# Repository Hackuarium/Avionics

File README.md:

# 9 outputs and 2 inputs

ACT4088 like in bioreactor:

Power supply

- LMR50410-Q1
- https://www.ti.com/lit/ds/symlink/lmr50410-q1.pdf?HQS=dis-mous-null-mousermode-dsf-pf-null-wwe&ts=1698122939216&ref_url=https%253A%252F%252Fwww.mouser.ch%252F

SO-8

- https://www.diodes.com/assets/Datasheets/AP64100Q.pdf - 10 external components
- https://www.diodes.com/assets/Datasheets/AP64202Q.pdf - 7 external components
- https://www.mouser.ch/datasheet/2/389/l6982-2303627.pdf - 7 external components

SOT-89

- https://www.mouser.ch/datasheet/2/294/NJW4132_E-1917720.pdf - NJW4132

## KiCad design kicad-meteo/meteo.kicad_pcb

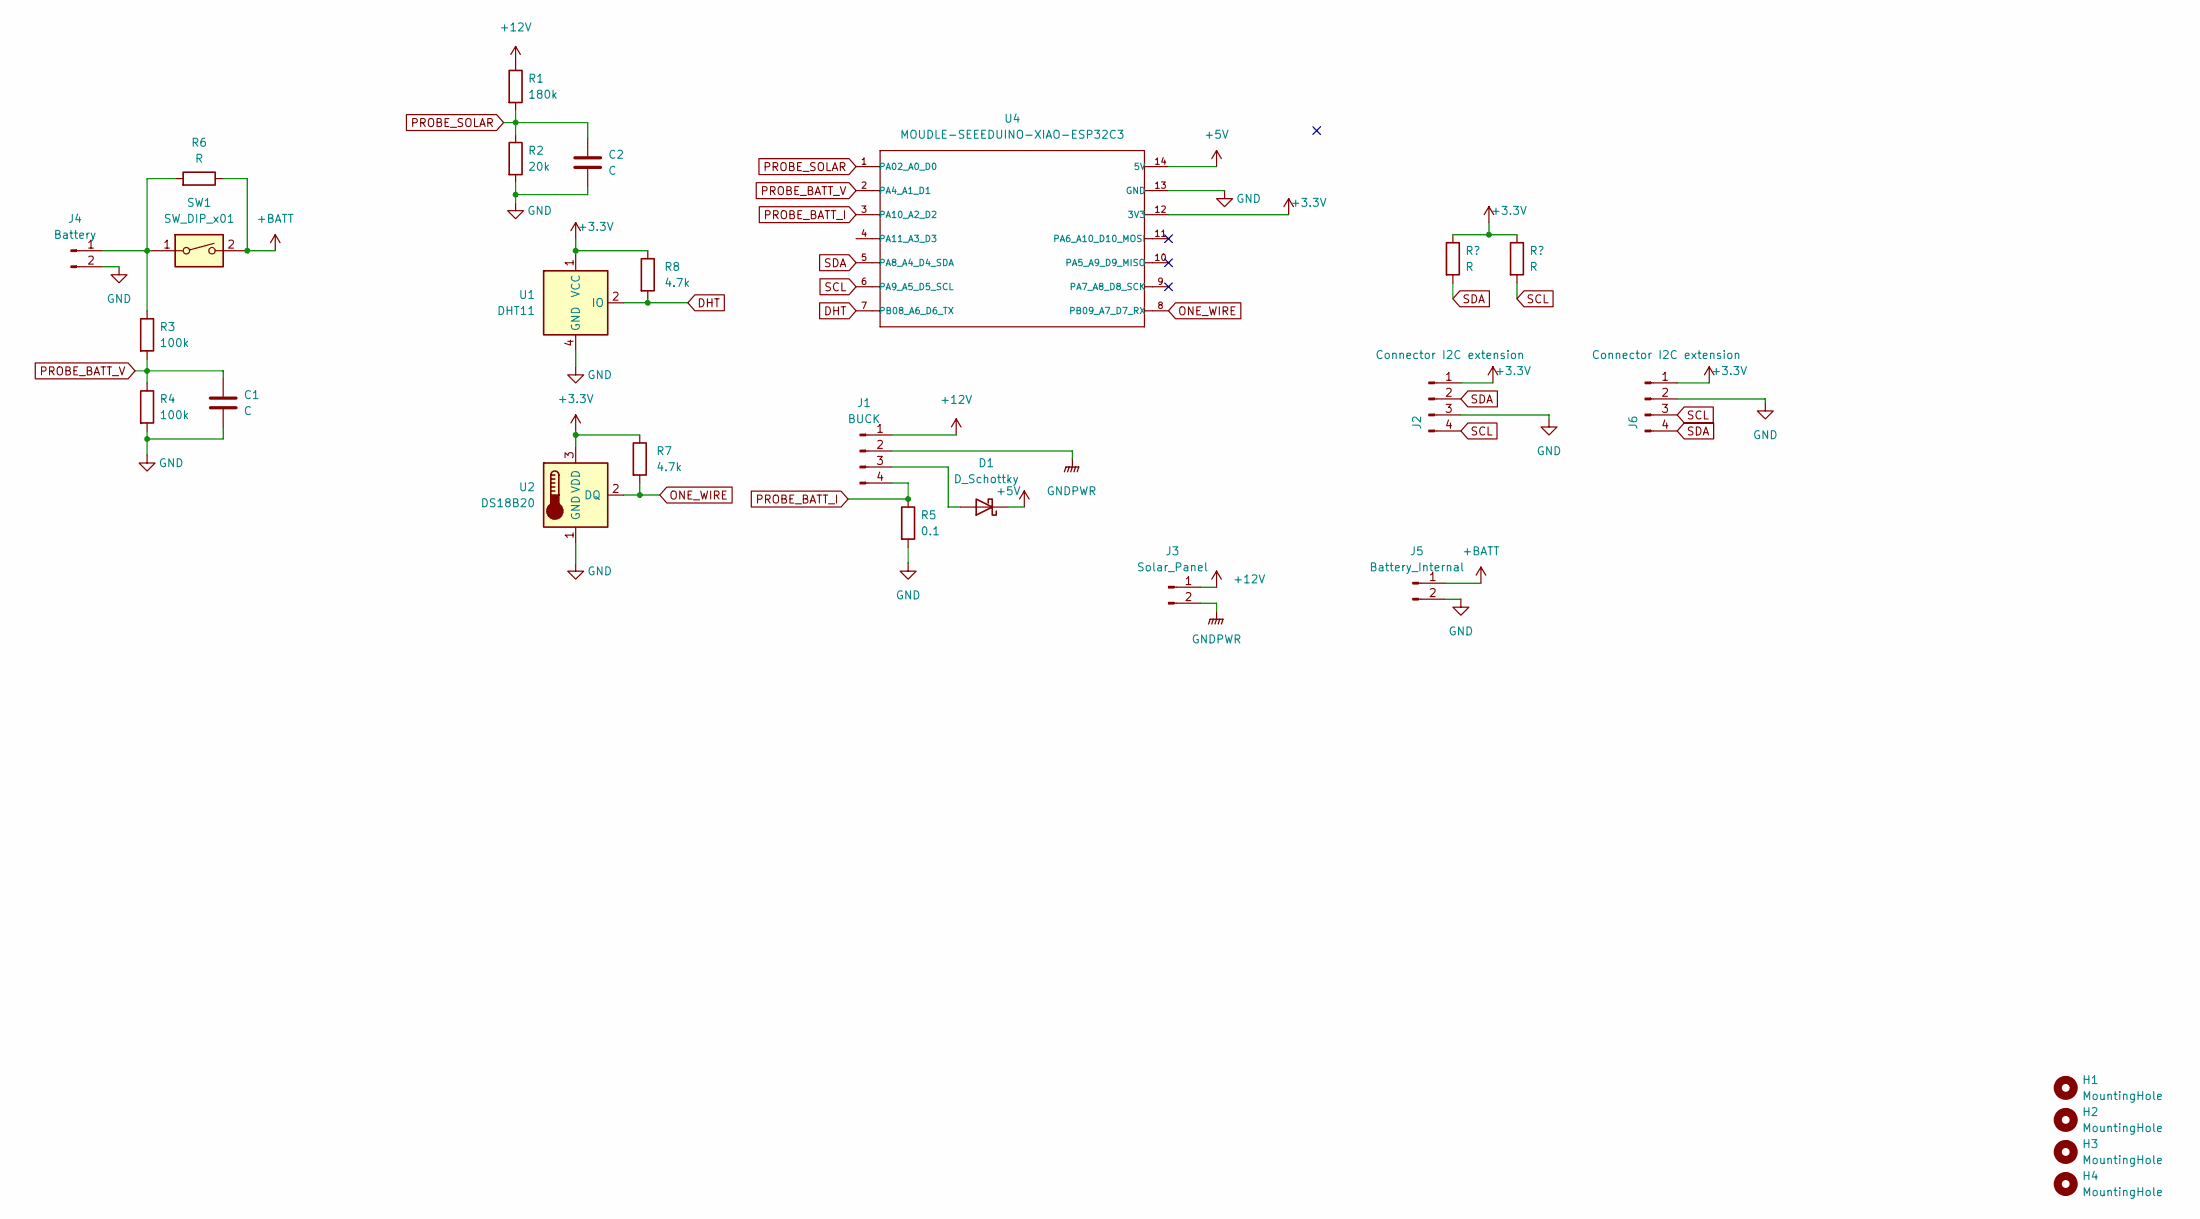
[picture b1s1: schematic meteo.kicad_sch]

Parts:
C1, C2: C; C_1206_3216Metric_Pad1.33x1.80mm_HandSolder
D1: D_Schottky; D_1206_3216Metric_Pad1.42x1.75mm_HandSolder
H1, H2, H3, H4: MountingHole; MountingHole_3.2mm_M3_ISO7380
J1: BUCK; BUCK 18x12mm
J2, J6: Connector I2C extension; PinHeader_1x04_P2.54mm_Vertical
J3: Solar_Panel; SolderWirePad_5.08x2
J4: Battery; SolderWirePad_5.08x2
J5: Battery_Internal; SolderWirePad_3x2
R1: 180k; R_1206_3216Metric_Pad1.30x1.75mm_HandSolder
R2: 20k; R_1206_3216Metric_Pad1.30x1.75mm_HandSolder
R3, R4: 100k; R_1206_3216Metric_Pad1.30x1.75mm_HandSolder
R5: 0.1; R_1206_3216Metric_Pad1.30x1.75mm_HandSolder
R6: R; R_1206_3216Metric_Pad1.30x1.75mm_HandSolder
R7, R8: 4.7k; R_1206_3216Metric_Pad1.30x1.75mm_HandSolder
SW1: SW_DIP_x01; SW_DIP_SPSTx01_Slide_9.78x4.72mm_W7.62mm_P2.54mm
U1: DHT11; Aosong_DHT11_5.5x12.0_P2.54mm
U2: DS18B20; PinHeader_1x03_P2.54mm_Vertical
U4: MOUDLE-SEEEDUINO-XIAO-ESP32C3; MOUDLE14P-SMD-2.54-21X17.8MM

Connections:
+3.3V: J2.1, J6.1, R7.1, R8.1, U1.1 (VCC), U2.3 (VDD), U4.12 (3V3)
+5V: D1.1 (K), U4.14 (5V)
+12V: J1.1, J3.1, R1.1
+BATT: J5.1, R6.1, SW1.2
DHT: R8.2, U1.2 (IO), U4.7 (PB08_A6_D6_TX)
GND: C1.2, C2.2, J2.3, J4.2, J5.2, J6.2, R2.2, R4.2, R5.2, U1.4 (GND), U2.1 (GND), U4.13 (GND)
GNDPWR: J1.2, J3.2
unnamed: D1.2 (A), J1.3
unnamed: J4.1, R3.1, R6.2, SW1.1
ONE_WIRE: R7.2, U2.2 (DQ), U4.8 (PB09_A7_D7_RX)
PROBE_BATT_I: J1.4, R5.1, U4.3 (PA10_A2_D2)
PROBE_BATT_V: C1.1, R3.2, R4.1, U4.2 (PA4_A1_D1)
PROBE_SOLAR: C2.1, R1.2, R2.1, U4.1 (PA02_A0_D0)
SCL: J2.4, J6.3, U4.6 (PA9_A5_D5_SCL)
SDA: J2.2, J6.4, U4.5 (PA8_A4_D4_SDA)

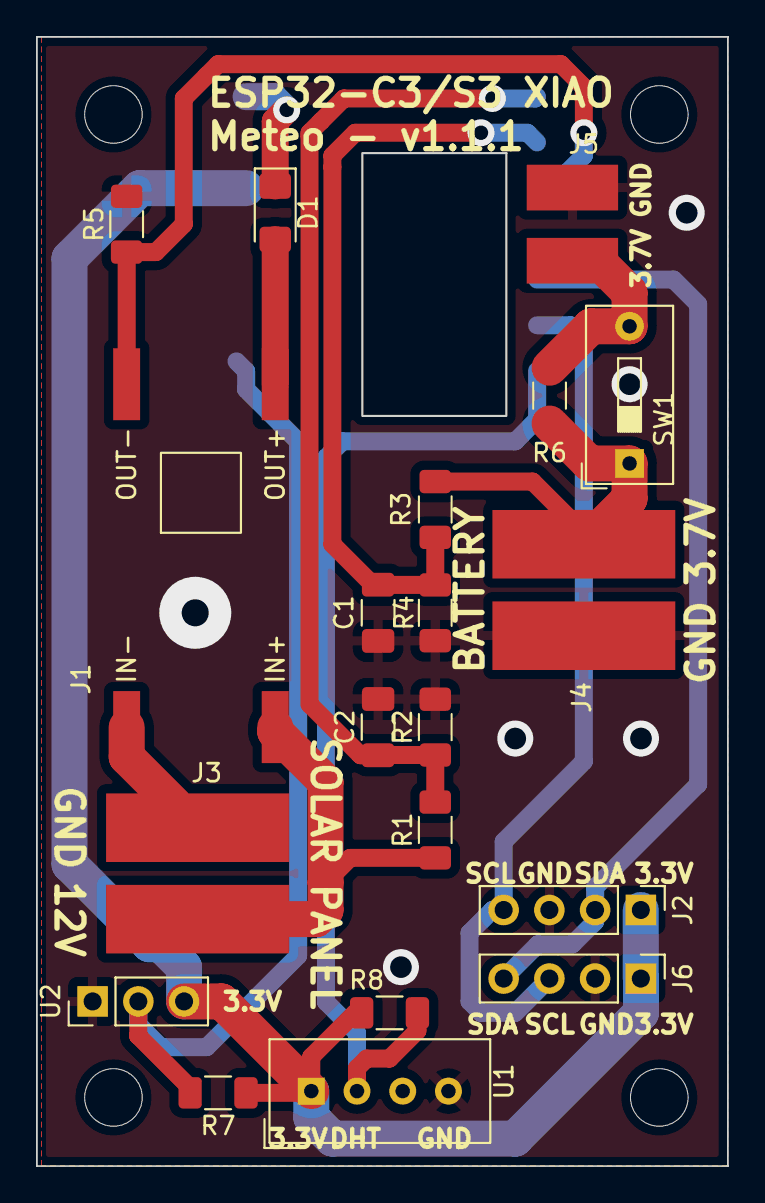
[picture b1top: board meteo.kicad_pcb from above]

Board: 2 copper layers, 38.4 x 62.7 mm, 25 parts (1 on the bottom side), 15 nets.

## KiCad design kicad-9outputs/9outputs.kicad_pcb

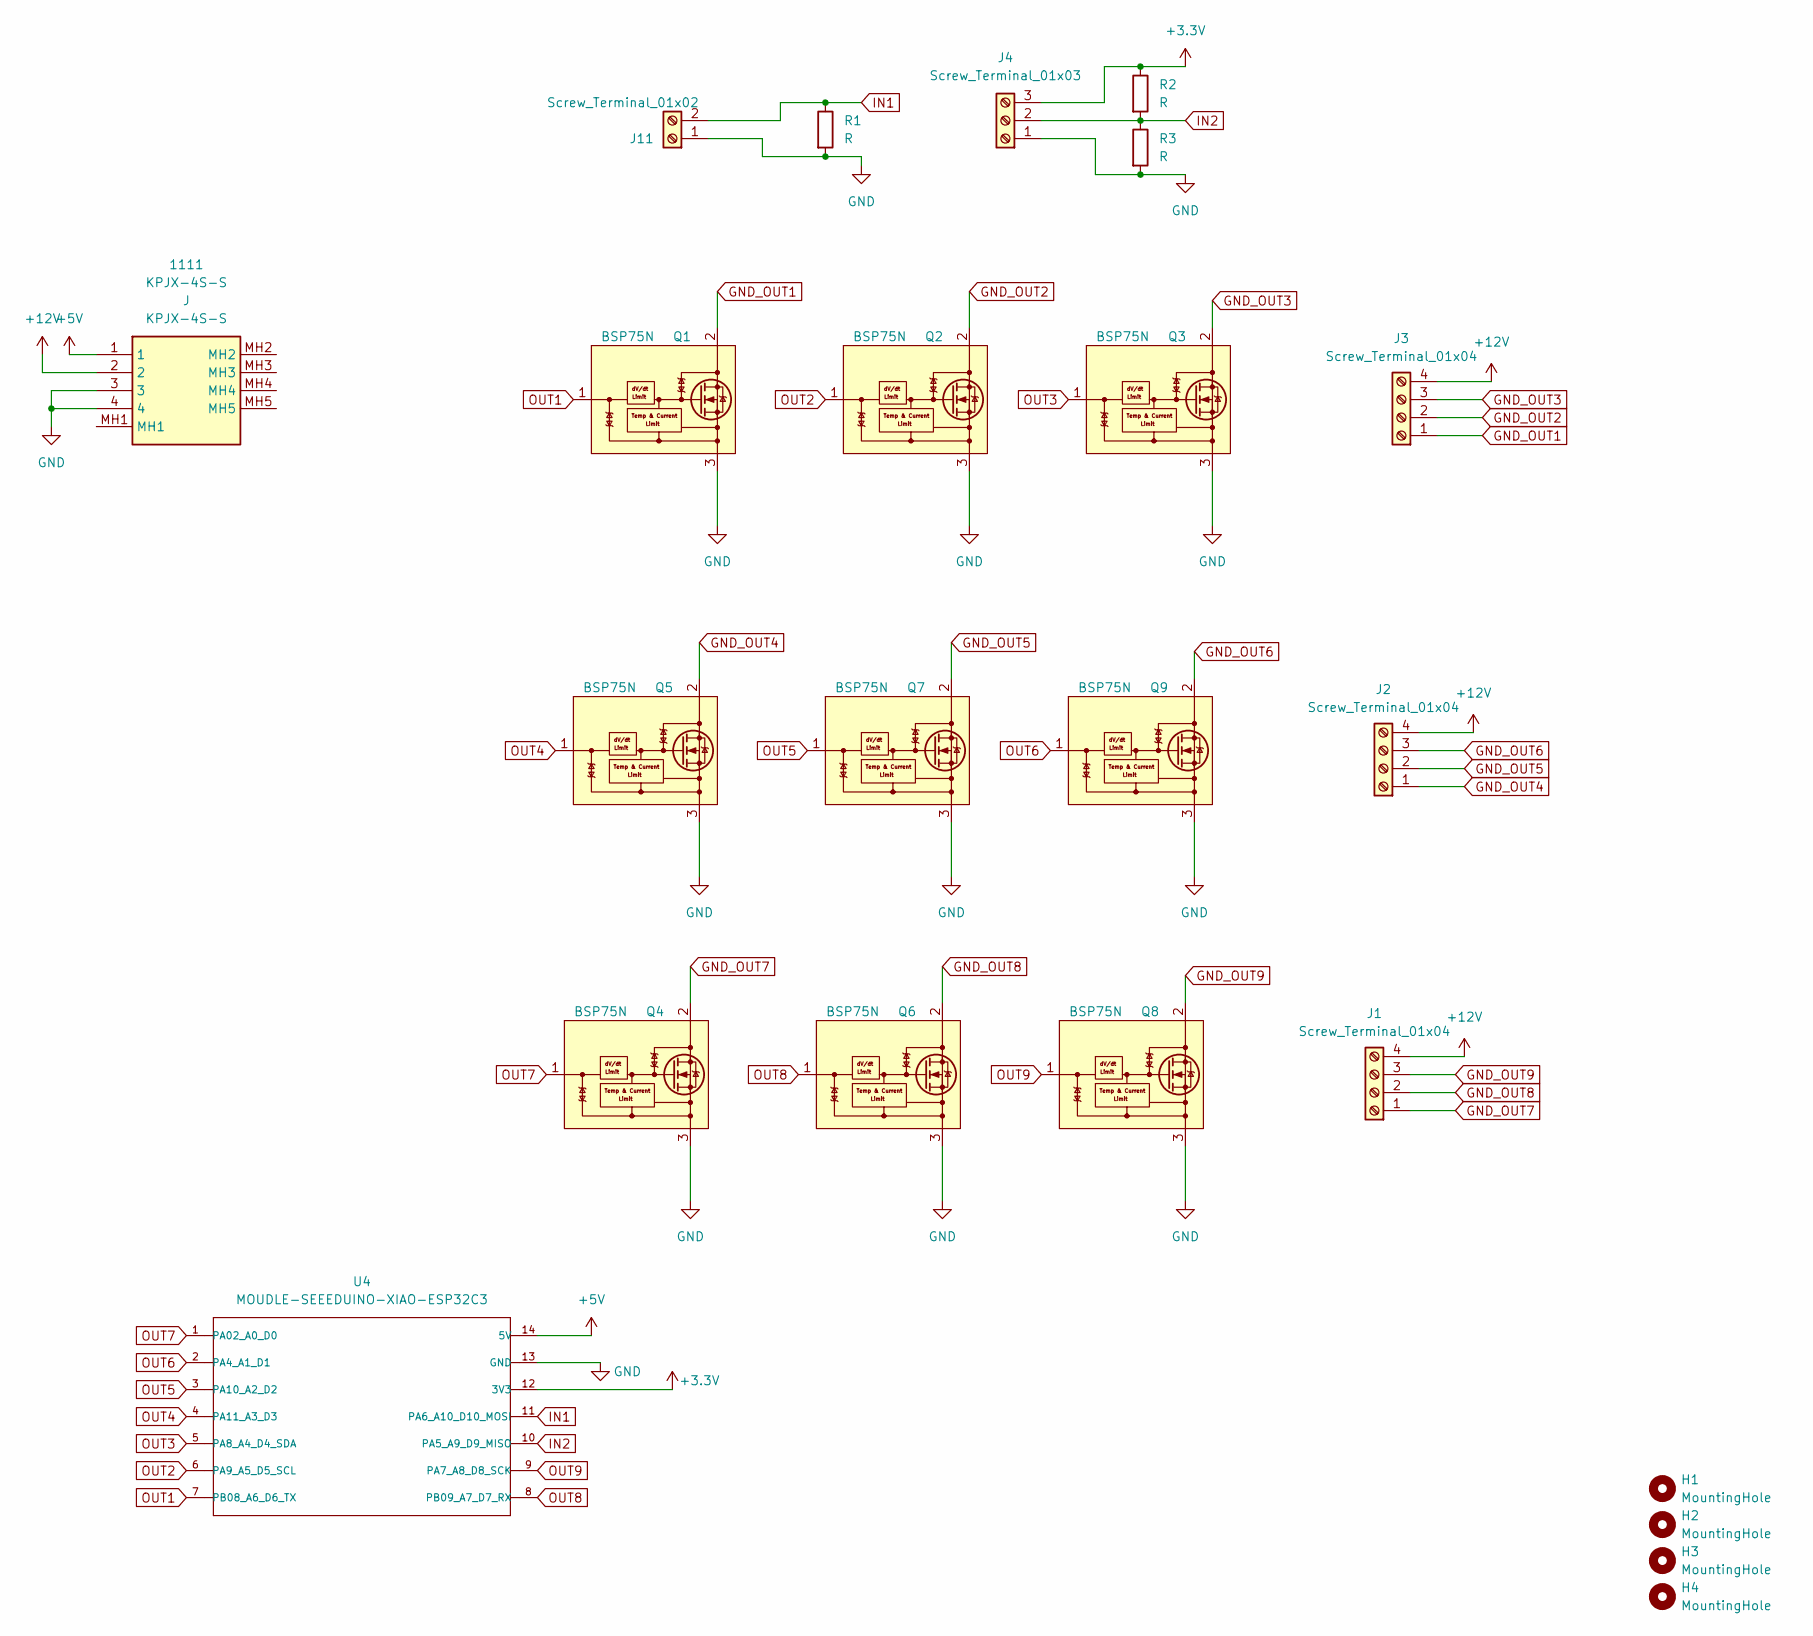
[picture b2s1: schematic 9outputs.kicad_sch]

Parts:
1111: KPJX-4S-S; KPJX4SS; Mouser Part Number 806-KPJX-4S-S
H1, H2, H3, H4: MountingHole; MountingHole_3.2mm_M3_ISO7380
J1, J2, J3: Screw_Terminal_01x04; TerminalBlock_MetzConnect_Type094_RT03504HBLU_1x04_P5.00mm_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
J4: Screw_Terminal_01x03; TerminalBlock_MetzConnect_Type094_RT03503HBLU_1x03_P5.00mm_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
J11: Screw_Terminal_01x02; TerminalBlock_MetzConnect_Type094_RT03502HBLU_1x02_P5.00mm_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
Q1, Q2, Q3, Q4, Q5, Q6, Q7, Q8, Q9: BSP75N; SOT-223
R1, R2, R3: R; R_1206_3216Metric_Pad1.30x1.75mm_HandSolder
U4: MOUDLE-SEEEDUINO-XIAO-ESP32C3; MOUDLE14P-SMD-2.54-21X17.8MM

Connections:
+3.3V: J4.3, R2.1, U4.12 (3V3)
+5V: 1111.1, U4.14 (5V)
+12V: 1111.2, J1.4, J2.4, J3.4
GND: 1111.3, 1111.4, J4.1, J11.1, Q1.3 (S), Q1.4 (S), Q2.3 (S), Q2.4 (S), Q3.3 (S), Q3.4 (S), Q4.3 (S), Q4.4 (S), Q5.3 (S), Q5.4 (S), Q6.3 (S), Q6.4 (S), Q7.3 (S), Q7.4 (S), Q8.3 (S), Q8.4 (S), Q9.3 (S), Q9.4 (S), R1.2, R3.2, U4.13 (GND)
GND_OUT1: J3.1, Q1.2 (D)
GND_OUT2: J3.2, Q2.2 (D)
GND_OUT3: J3.3, Q3.2 (D)
GND_OUT4: J2.1, Q5.2 (D)
GND_OUT5: J2.2, Q7.2 (D)
GND_OUT6: J2.3, Q9.2 (D)
GND_OUT7: J1.1, Q4.2 (D)
GND_OUT8: J1.2, Q6.2 (D)
GND_OUT9: J1.3, Q8.2 (D)
IN1: J11.2, R1.1, U4.11 (PA6_A10_D10_MOSI)
IN2: J4.2, R2.2, R3.1, U4.10 (PA5_A9_D9_MISO)
OUT1: Q1.1 (G), U4.7 (PB08_A6_D6_TX)
OUT2: Q2.1 (G), U4.6 (PA9_A5_D5_SCL)
OUT3: Q3.1 (G), U4.5 (PA8_A4_D4_SDA)
OUT4: Q5.1 (G), U4.4 (PA11_A3_D3)
OUT5: Q7.1 (G), U4.3 (PA10_A2_D2)
OUT6: Q9.1 (G), U4.2 (PA4_A1_D1)
OUT7: Q4.1 (G), U4.1 (PA02_A0_D0)
OUT8: Q6.1 (G), U4.8 (PB09_A7_D7_RX)
OUT9: Q8.1 (G), U4.9 (PA7_A8_D8_SCK)

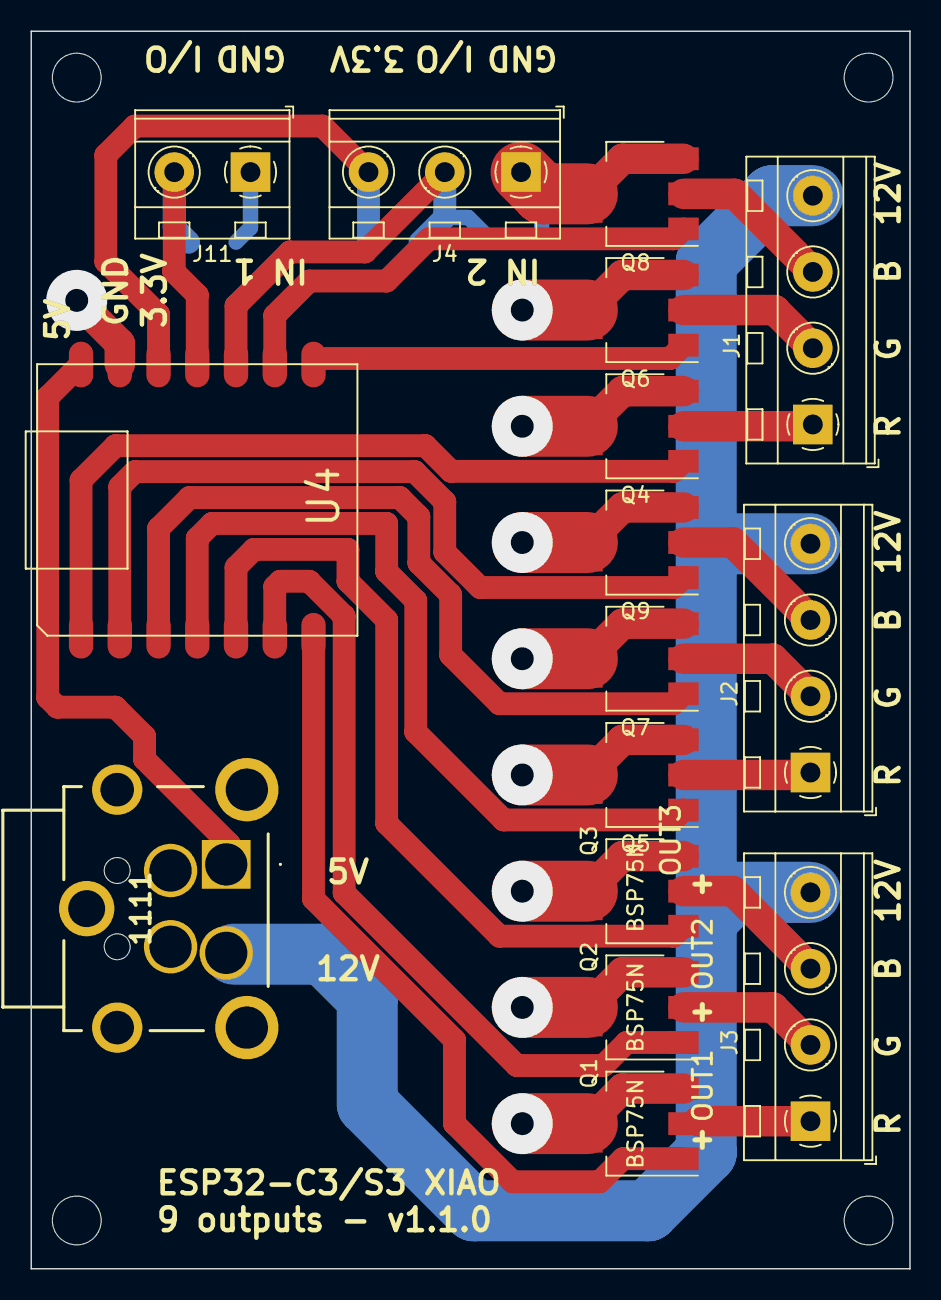
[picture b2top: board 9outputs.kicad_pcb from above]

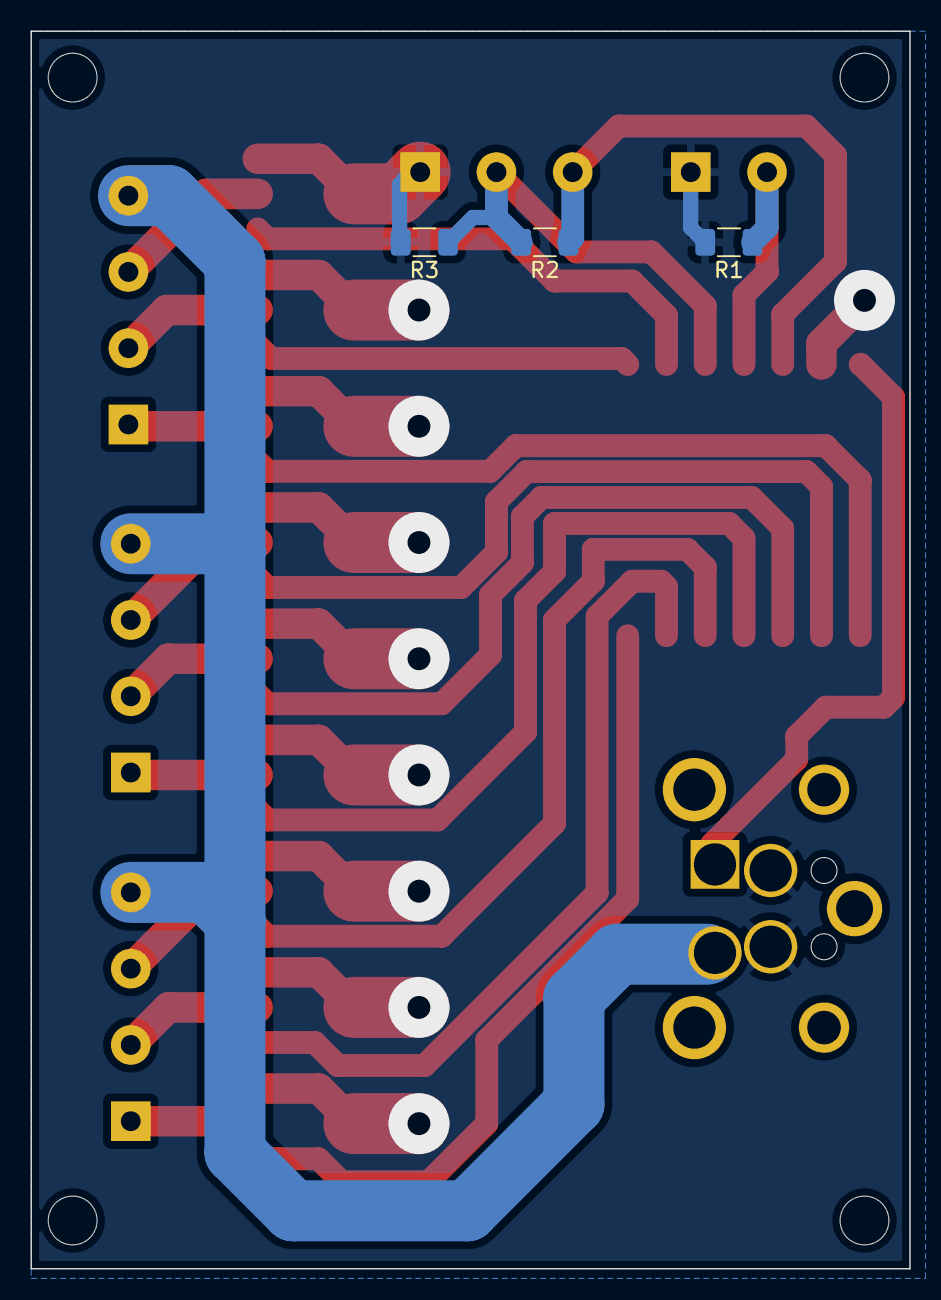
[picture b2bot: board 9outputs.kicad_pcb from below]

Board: 2 copper layers, 57.6 x 81.1 mm, 23 parts (3 on the bottom side), 24 nets.

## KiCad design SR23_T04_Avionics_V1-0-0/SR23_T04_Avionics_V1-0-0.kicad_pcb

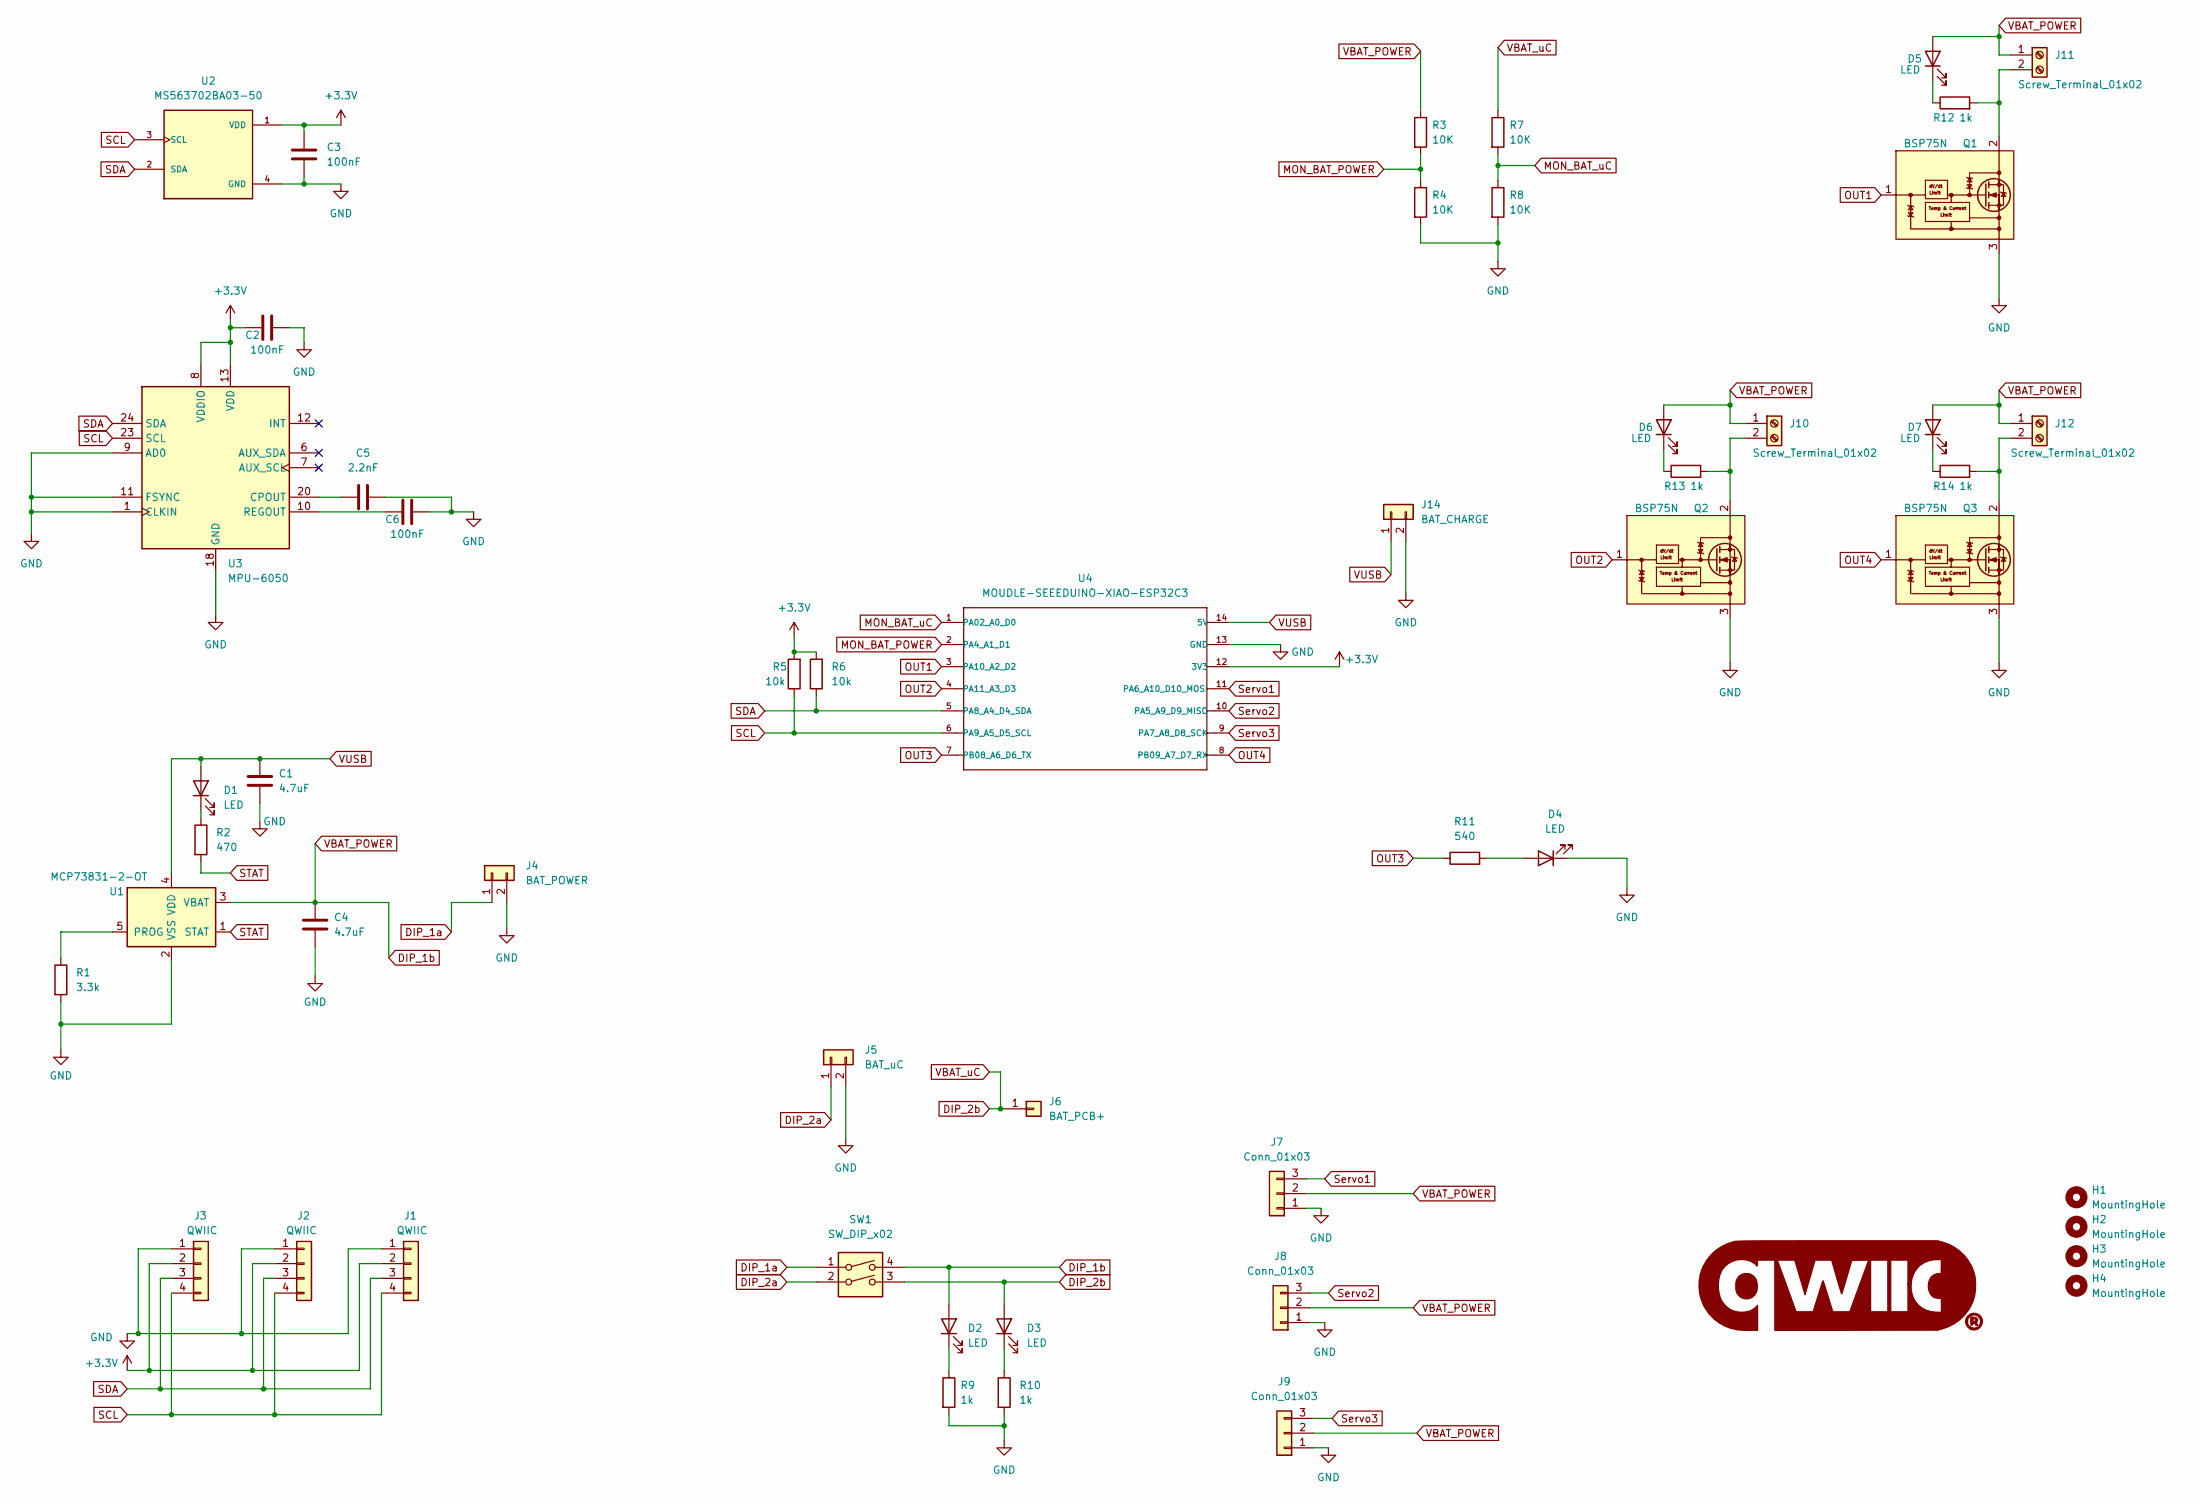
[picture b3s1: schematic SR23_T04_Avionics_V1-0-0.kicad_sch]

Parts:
C1, C4: 4.7uF; C_0805_2012Metric_Pad1.18x1.45mm_HandSolder
C2, C3, C6: 100nF; C_0805_2012Metric_Pad1.18x1.45mm_HandSolder
C5: 2.2nF; C_0805_2012Metric_Pad1.18x1.45mm_HandSolder
D1, D2, D3, D4, D5, D6, D7: LED; LED_0805_2012Metric_Pad1.15x1.40mm_HandSolder
H1, H2, H3, H4: MountingHole; MountingHole_3.2mm_M3_ISO7380
J1, J2, J3: QWIIC; JST_SH_SM04B-SRSS-TB_1x04-1MP_P1.00mm_Horizontal
J4: BAT_POWER; JST_XH_B2B-XH-A_1x02_P2.50mm_Vertical
J5: BAT_uC; JST_XH_B2B-XH-A_1x02_P2.50mm_Vertical
J6: BAT_PCB+; PinHeader_1x01_P2.54mm_Vertical
J7, J8, J9: Conn_01x03; PinHeader_1x03_P2.54mm_Vertical
J10, J11, J12: Screw_Terminal_01x02; TerminalBlock_MetzConnect_Type086_RT03402HBLC_1x02_P3.81mm_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
J14: BAT_CHARGE; PinHeader_2x01_P2.54mm_Vertical
Q1, Q2, Q3: BSP75N; SOT-223
R1: 3.3k; R_0805_2012Metric_Pad1.20x1.40mm_HandSolder
R2: 470; R_0805_2012Metric_Pad1.20x1.40mm_HandSolder
R3, R4, R7, R8: 10K; R_0805_2012Metric_Pad1.20x1.40mm_HandSolder
R5, R6: 10k; R_0805_2012Metric_Pad1.20x1.40mm_HandSolder
R9, R10, R12, R13, R14: 1k; R_0805_2012Metric_Pad1.20x1.40mm_HandSolder
R11: 540; R_0805_2012Metric_Pad1.20x1.40mm_HandSolder
SW1: SW_DIP_x02; SW_DIP_SPSTx02_Slide_9.78x7.26mm_W7.62mm_P2.54mm
U1: MCP73831-2-OT; SOT-23-5
U2: MS563702BA03-50; TE_MS563702BA03-50
U3: MPU-6050; InvenSense_QFN-24_4x4mm_P0.5mm
U4: MOUDLE-SEEEDUINO-XIAO-ESP32C3; MOUDLE14P-SMD-2.54-21X17.8MM

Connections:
+3.3V: C2.1, C3.1, J1.2, J2.2, J3.2, R5.2, R6.2, U2.1 (VDD), U3.8 (VDDIO), U3.13 (VDD), U4.12 (3V3)
DIP_1a: J4.1, SW1.1
DIP_1b: C4.1, D2.2 (A), D5.2 (A), D6.2 (A), D7.2 (A), J7.2, J8.2, J9.2, J10.1, J11.1, J12.1, R3.1, SW1.4, U1.3 (VBAT)
DIP_2a: J5.1, SW1.2
DIP_2b: D3.2 (A), J6.1, R7.1, SW1.3
GND: C1.2, C2.2, C3.2, C4.2, C5.2, C6.2, D4.1 (K), J1.1, J2.1, J3.1, J4.2, J5.2, J7.1, J8.1, J9.1, J14.2, Q1.3 (S), Q1.4 (S), Q2.3 (S), Q2.4 (S), Q3.3 (S), Q3.4 (S), R1.2, R4.2, R8.2, R9.2, R10.2, U1.2 (VSS), U2.4 (GND), U3.1 (CLKIN), U3.9 (AD0), U3.11 (FSYNC), U3.18 (GND), U4.13 (GND)
MON_BAT_POWER: R3.2, R4.1, U4.2 (PA4_A1_D1)
MON_BAT_uC: R7.2, R8.1, U4.1 (PA02_A0_D0)
unnamed: C5.1, U3.20 (CPOUT)
unnamed: C6.1, U3.10 (REGOUT)
unnamed: D1.1 (K), R2.1
unnamed: D2.1 (K), R9.1
unnamed: D3.1 (K), R10.1
unnamed: D4.2 (A), R11.2
unnamed: D5.1 (K), R12.1
unnamed: D6.1 (K), R13.1
unnamed: D7.1 (K), R14.1
unnamed: J10.2, Q2.2 (D), R13.2
unnamed: J11.2, Q1.2 (D), R12.2
unnamed: J12.2, Q3.2 (D), R14.2
unnamed: R1.1, U1.5 (PROG)
OUT1: Q1.1 (G), U4.3 (PA10_A2_D2)
OUT2: Q2.1 (G), U4.4 (PA11_A3_D3)
OUT3: R11.1, U4.7 (PB08_A6_D6_TX)
OUT4: Q3.1 (G), U4.8 (PB09_A7_D7_RX)
SCL: J1.4, J2.4, J3.4, R5.1, U2.3 (SCL), U3.23 (SCL), U4.6 (PA9_A5_D5_SCL)
SDA: J1.3, J2.3, J3.3, R6.1, U2.2 (SDA), U3.24 (SDA), U4.5 (PA8_A4_D4_SDA)
STAT: R2.2, U1.1 (STAT)
Servo1: J7.3, U4.11 (PA6_A10_D10_MOSI)
Servo2: J8.3, U4.10 (PA5_A9_D9_MISO)
Servo3: J9.3, U4.9 (PA7_A8_D8_SCK)
VUSB: C1.1, D1.2 (A), J14.1, U1.4 (VDD), U4.14 (5V)

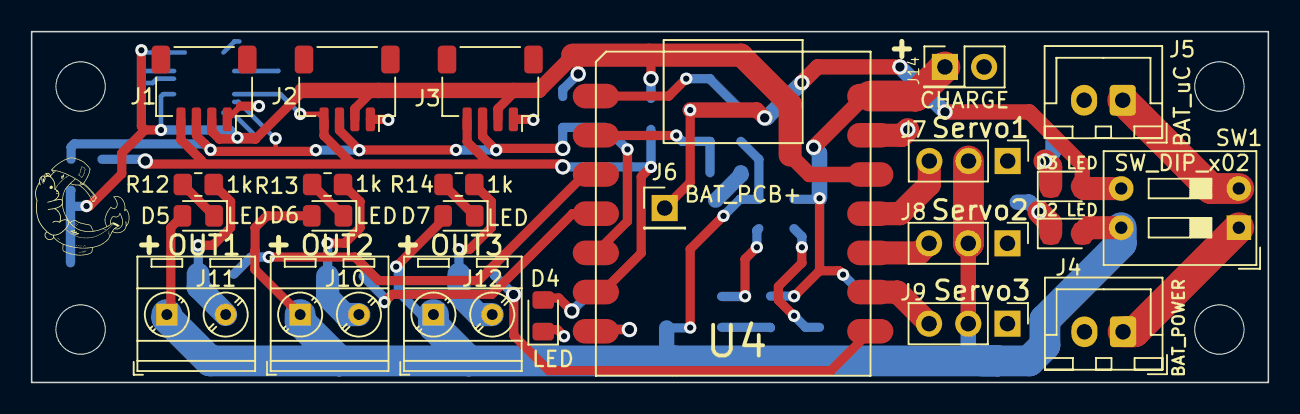
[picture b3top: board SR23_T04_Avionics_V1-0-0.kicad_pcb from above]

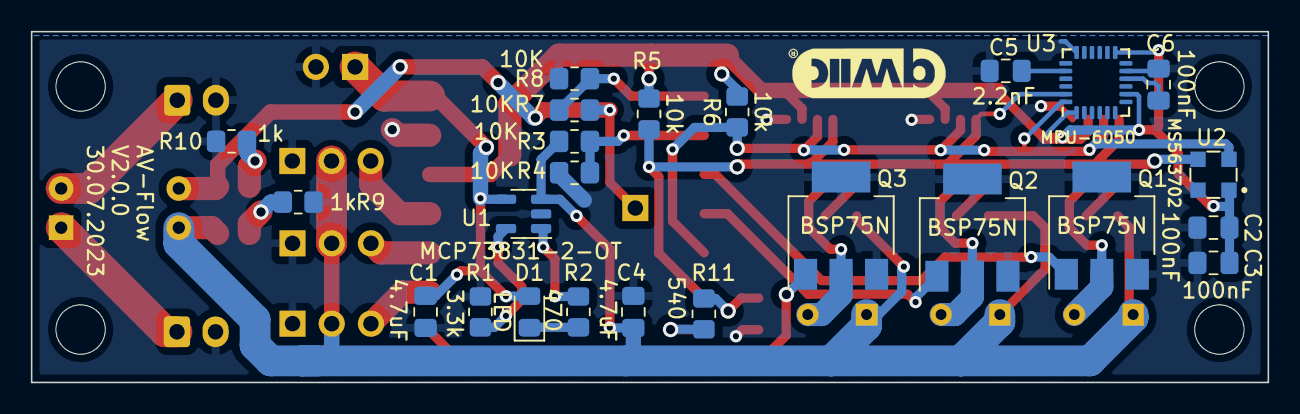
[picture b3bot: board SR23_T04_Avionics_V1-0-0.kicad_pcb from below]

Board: 2 copper layers, 80.1 x 22.7 mm, 52 parts (24 on the bottom side), 32 nets.

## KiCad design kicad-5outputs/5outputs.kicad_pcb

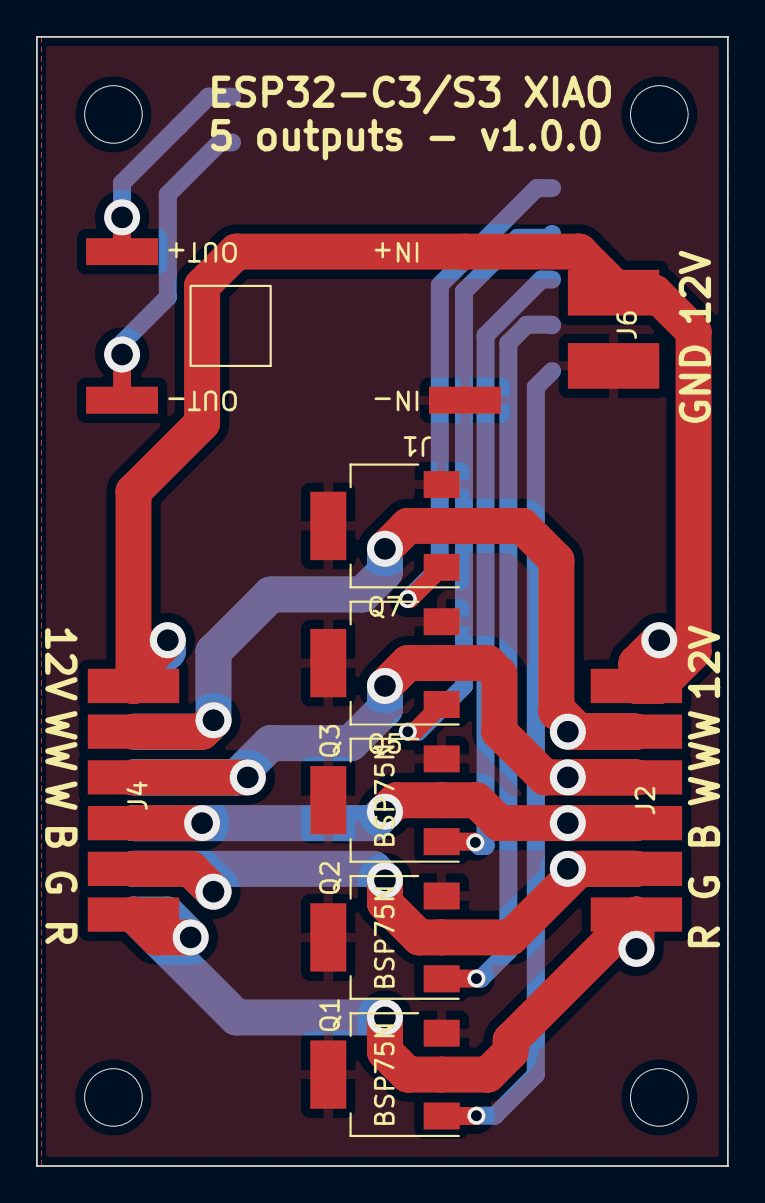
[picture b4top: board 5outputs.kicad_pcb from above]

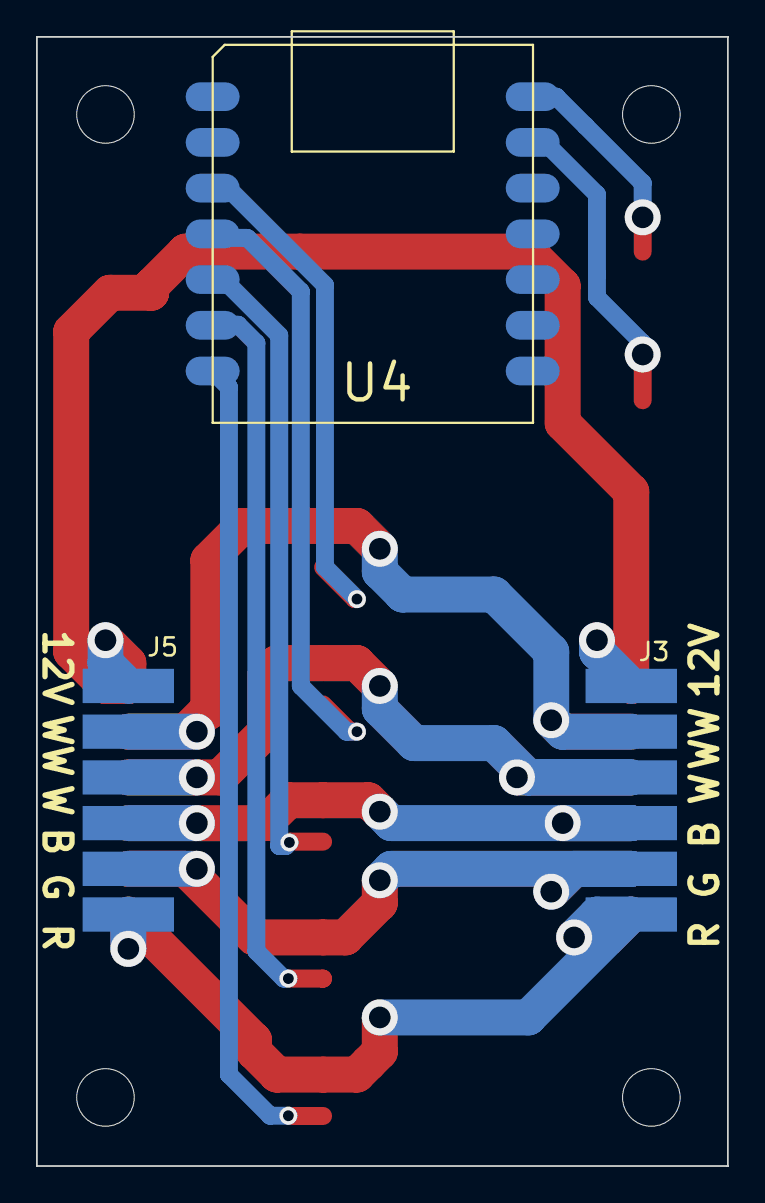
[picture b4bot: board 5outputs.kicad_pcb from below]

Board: 2 copper layers, 38.4 x 62.7 mm, 16 parts (3 on the bottom side), 14 nets.

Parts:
H1, H2, H3, H4: MountingHole; MountingHole_3.2mm_M3_ISO7380
J1: Conn_01x04_Male; BUCK 18x12mm
J2, J3, J4, J5: Conn_01x06_Male; SolderWirePad_2.54x6
J6: Conn_01x02_Male; SolderWirePad_3x2
Q1, Q2, Q3, Q5, Q7: BSP75N; SOT-223
U4: MOUDLE-SEEEDUINO-XIAO-ESP32C3; MOUDLE14P-SMD-2.54-21X17.8MM

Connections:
+5V: J1.3, U4.14 (5V)
+12V: J1.1, J2.1, J3.1, J4.1, J5.1, J6.1
GND: J1.4, U4.13 (GND)
GNDPWR: J1.2, J6.2, Q1.3 (S), Q1.4 (S), Q2.3 (S), Q2.4 (S), Q3.3 (S), Q3.4 (S), Q5.3 (S), Q5.4 (S), Q7.3 (S), Q7.4 (S)
GND_OUT1: J2.6, J3.6, J4.6, J5.6, Q1.2 (D)
GND_OUT2: J2.5, J3.5, J4.5, J5.5, Q2.2 (D)
GND_OUT3: J2.4, J3.4, J4.4, J5.4, Q3.2 (D)
GND_OUT4: J2.3, J3.3, J4.3, J5.3, Q5.2 (D)
GND_OUT5: J2.2, J3.2, J4.2, J5.2, Q7.2 (D)
OUT1: Q1.1 (G), U4.7 (PB08_A6_D6_TX)
OUT2: Q2.1 (G), U4.6 (PA9_A5_D5_SCL)
OUT3: Q3.1 (G), U4.5 (PA8_A4_D4_SDA)
OUT4: Q5.1 (G), U4.4 (PA11_A3_D3)
OUT5: Q7.1 (G), U4.3 (PA10_A2_D2)

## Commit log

2023-04-10 wip: pcb and md documentation
2023-04-10 wip: PCB rooting
2023-04-11 wip: working on avionics
2023-04-11 wip: rooting of the board completed - waiting on review
2023-04-11 t "wip: make the layers visible on the baord in Kicad"
2023-07-23 feat: Version 1.0.0 of the AV-Flow PCB
2023-07-29 wip: PCB V2
2023-07-30 feat: new board V2 dual sided
    closes: https://github.com/Hackuarium/Avionics/issues/7
2023-11-19 feat: add program
2023-11-19 chore: remoe old files
2023-11-19 feat: deal correctly with 3 rgb channels
2025-03-27 feat: add 5 outputs
2025-06-22 feat: add meteo v100
2025-06-29 feat(meteo): fix pin mapping and add switch, v1.1.0
2025-06-29 fix: add pull-up for DHT-22
2025-11-09 fix: correct AD pin for monitoring and ground
